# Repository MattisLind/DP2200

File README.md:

# Datapoint 2200

The restoration of this Datapoint 2200 is now finished and it is mostly working perfectly. One of the tape drives are bit finicky when it is cold though.

It was a long journey that involved creating a simulator, make extender boards and a PSU that can be used while debugging the machine to avoid getting killed (the original PSU is hazardous). In the end there were one single TTL chip that was bad.

The purpose of this repo is to describe the effort in restoring a Datapoint 2200 that I received as an IKEA-kit. This will include documenting all the parts of the machine as well as create a simulator for it.

I received this Datapoint 2200 (Version II) as a trade with a German collector for a Q1 computersystem. The 2200 was delivered as a kit, but I am pretty sure all parts are present. The goal is to revive this very interesting milestone in computer history. It can be considered as the first personal computer (depending on definition) and is also the beginning of x86 archicture whis still is omnipresent.

There are two versions of the Datapoint 2200. Version I was a serial implementation where the memory was built out of dynamic MOS shiftregisters. The reason for this was that random access memory chips wasn't available yet. The ALU was also implemented in serial fashion handling one bit at a time. This also meant that all regsisters (A,B,C,D,E,H,L) were 8-bit shiftregisters. The serial implementation of course made the CPU very slow. An instruction could take 16 microseconds to execute and this didn't include instruction fetch or memory references. Memory accesses could take up to 520 mircoseconds since the memory essentially was a long loop of bits that has to be shifted to the correct position to be accessed.

Later on Datapoint asked both Intel and Texas to design a MOS chip for the architecture of the Datapoint 2200. Both vendors came up with a chip but at that time Datapoint already decided to go for a parallell variant of the CPU using the now available RAM chips. The version II used 1k Dyanmic RAM chips (Mostek MK 4006) and a 8 bit parallell ALU using two 74181.

## Power supply

The PSU is the right half in the pricture above and sits in the back of the unit. But the CPU is not selfcontained. The 50 pin connector is connected to a backplane where the control logic for the PSU is located. Since this logic is on the hot side there a live voltages in the backplane. The transistors on the back of the big heatsink the PSU is mounted to also are a line voltage. One has to be careful when working with this PSU...

The design of the PSU is quite peculiar and is not looking like any other switch mode PSU I have seen. There is a buck-converter directly off the rectified AC input which steps down from line-voltage to around 60. The control-logic is designed to regulate to this voltage. The 60V DC levels is then converted into 5V and other outputs using a self-resonant push-pull design. There is also a crowbar protecting it so that the 60V DC may never reach above 77V.

Control-logic is on a board in the backplane.

## Simulator

I decided that a simulator would be useful to have when trying to debug and then also perhaps write small programs for this machine. I found a 8008 simulator which looked quite promising and did quite some adaptations for it to to run Datapoint 2200 code. The simulator is very much work in progress and is far from finished. I.e. non-working.

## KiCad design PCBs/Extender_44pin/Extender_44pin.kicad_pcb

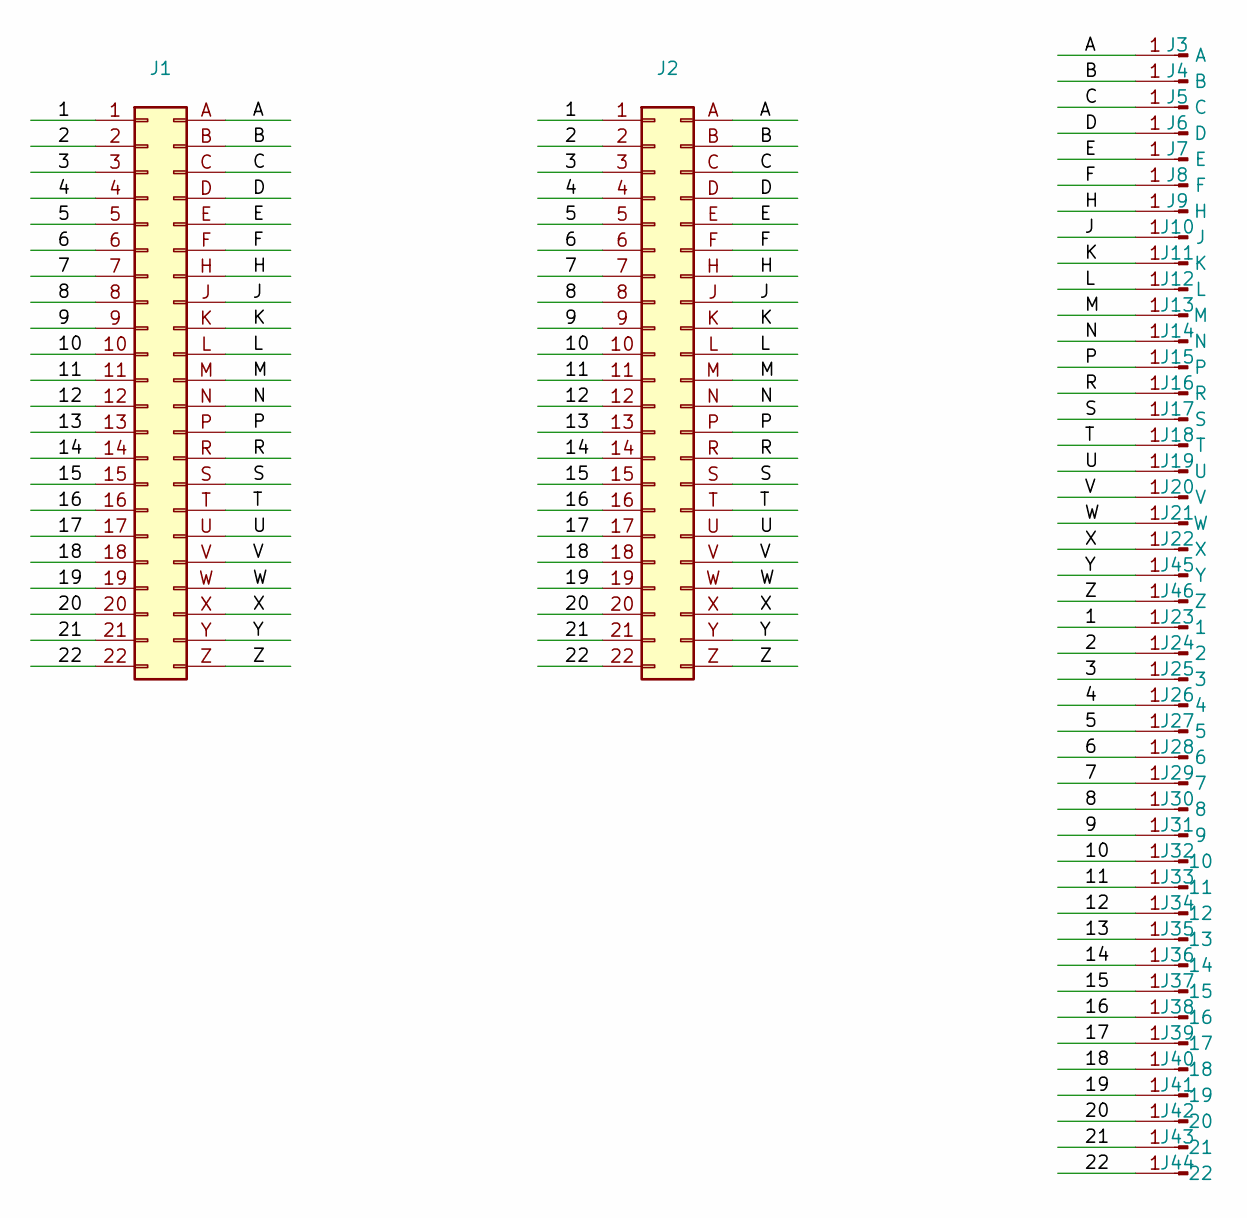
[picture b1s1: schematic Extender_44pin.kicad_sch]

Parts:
J1: Datapoint_2200_44pin_female
J2: Datapoint_2200_44pin_male
J3: A; PinHeader_1x01_P2.54mm_Vertical
J4: B; PinHeader_1x01_P2.54mm_Vertical
J5: C; PinHeader_1x01_P2.54mm_Vertical
J6: D; PinHeader_1x01_P2.54mm_Vertical
J7: E; PinHeader_1x01_P2.54mm_Vertical
J8: F; PinHeader_1x01_P2.54mm_Vertical
J9: H; PinHeader_1x01_P2.54mm_Vertical
J10: J; PinHeader_1x01_P2.54mm_Vertical
J11: K; PinHeader_1x01_P2.54mm_Vertical
J12: L; PinHeader_1x01_P2.54mm_Vertical
J13: M; PinHeader_1x01_P2.54mm_Vertical
J14: N; PinHeader_1x01_P2.54mm_Vertical
J15: P; PinHeader_1x01_P2.54mm_Vertical
J16: R; PinHeader_1x01_P2.54mm_Vertical
J17: S; PinHeader_1x01_P2.54mm_Vertical
J18: T; PinHeader_1x01_P2.54mm_Vertical
J19: U; PinHeader_1x01_P2.54mm_Vertical
J20: V; PinHeader_1x01_P2.54mm_Vertical
J21: W; PinHeader_1x01_P2.54mm_Vertical
J22: X; PinHeader_1x01_P2.54mm_Vertical
J23: 1; PinHeader_1x01_P2.54mm_Vertical
J24: 2; PinHeader_1x01_P2.54mm_Vertical
J25: 3; PinHeader_1x01_P2.54mm_Vertical
J26: 4; PinHeader_1x01_P2.54mm_Vertical
J27: 5; PinHeader_1x01_P2.54mm_Vertical
J28: 6; PinHeader_1x01_P2.54mm_Vertical
J29: 7; PinHeader_1x01_P2.54mm_Vertical
J30: 8; PinHeader_1x01_P2.54mm_Vertical
J31: 9; PinHeader_1x01_P2.54mm_Vertical
J32: 10; PinHeader_1x01_P2.54mm_Vertical
J33: 11; PinHeader_1x01_P2.54mm_Vertical
J34: 12; PinHeader_1x01_P2.54mm_Vertical
J35: 13; PinHeader_1x01_P2.54mm_Vertical
J36: 14; PinHeader_1x01_P2.54mm_Vertical
J37: 15; PinHeader_1x01_P2.54mm_Vertical
J38: 16; PinHeader_1x01_P2.54mm_Vertical
J39: 17; PinHeader_1x01_P2.54mm_Vertical
J40: 18; PinHeader_1x01_P2.54mm_Vertical
J41: 19; PinHeader_1x01_P2.54mm_Vertical
J42: 20; PinHeader_1x01_P2.54mm_Vertical
J43: 21; PinHeader_1x01_P2.54mm_Vertical
J44: 22; PinHeader_1x01_P2.54mm_Vertical
J45: Y; PinHeader_1x01_P2.54mm_Vertical
J46: Z; PinHeader_1x01_P2.54mm_Vertical

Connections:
/1: J1.1, J2.1, J23.1
/2: J1.2, J2.2, J24.1
/3: J1.3, J2.3, J25.1
/4: J1.4, J2.4, J26.1
/5: J1.5, J2.5, J27.1
/6: J1.6, J2.6, J28.1
/7: J1.7, J2.7, J29.1
/8: J1.8, J2.8, J30.1
/9: J1.9, J2.9, J31.1
/10: J1.10, J2.10, J32.1
/11: J1.11, J2.11, J33.1
/12: J1.12, J2.12, J34.1
/13: J1.13, J2.13, J35.1
/14: J1.14, J2.14, J36.1
/15: J1.15, J2.15, J37.1
/16: J1.16, J2.16, J38.1
/17: J1.17, J2.17, J39.1
/18: J1.18, J2.18, J40.1
/19: J1.19, J2.19, J41.1
/20: J1.20, J2.20, J42.1
/21: J1.21, J2.21, J43.1
/22: J1.22, J2.22, J44.1
/A: J1.A, J2.A, J3.1
/B: J1.B, J2.B, J4.1
/C: J1.C, J2.C, J5.1
/D: J1.D, J2.D, J6.1
/E: J1.E, J2.E, J7.1
/F: J1.F, J2.F, J8.1
/H: J1.H, J2.H, J9.1
/J: J1.J, J2.J, J10.1
/K: J1.K, J2.K, J11.1
/L: J1.L, J2.L, J12.1
/M: J1.M, J2.M, J13.1
/N: J1.N, J2.N, J14.1
/P: J1.P, J2.P, J15.1
/R: J1.R, J2.R, J16.1
/S: J1.S, J2.S, J17.1
/T: J1.T, J2.T, J18.1
/U: J1.U, J2.U, J19.1
/V: J1.V, J2.V, J20.1
/W: J1.W, J2.W, J21.1
/X: J1.X, J2.X, J22.1
/Y: J1.Y, J2.Y, J45.1
/Z: J1.Z, J2.Z, J46.1

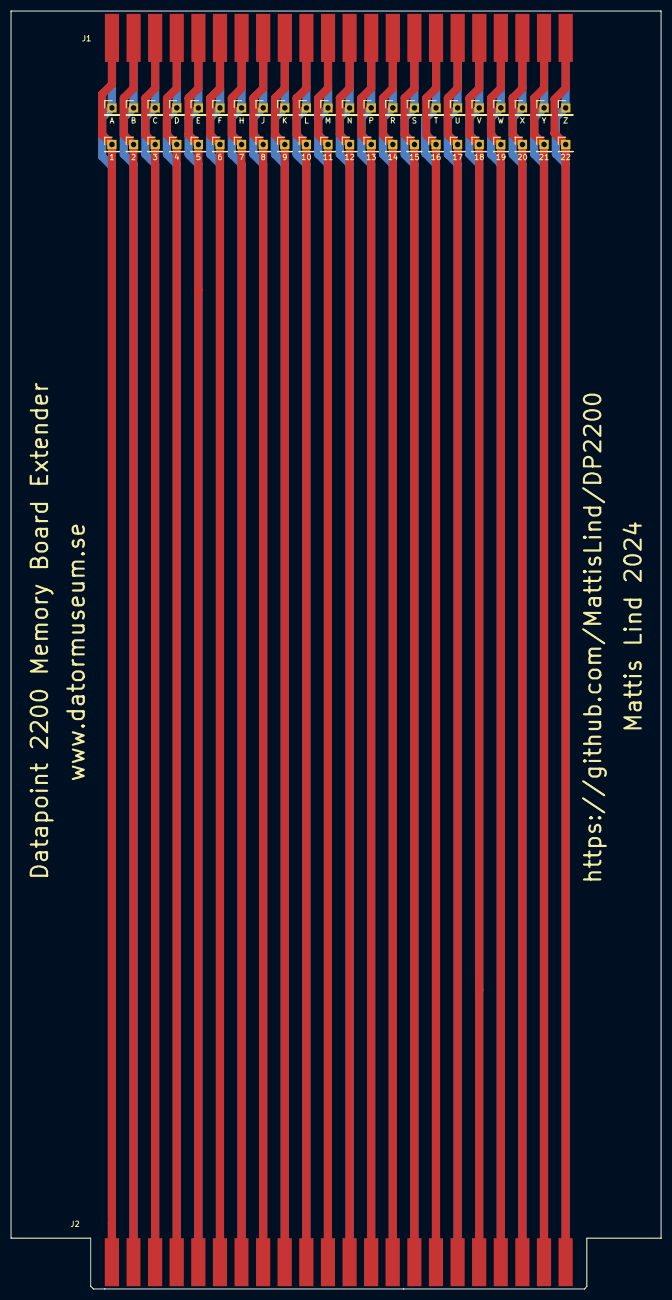
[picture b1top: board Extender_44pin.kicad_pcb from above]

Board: 2 copper layers, 119.1 x 234.2 mm, 46 parts (0 on the bottom side), 44 nets.

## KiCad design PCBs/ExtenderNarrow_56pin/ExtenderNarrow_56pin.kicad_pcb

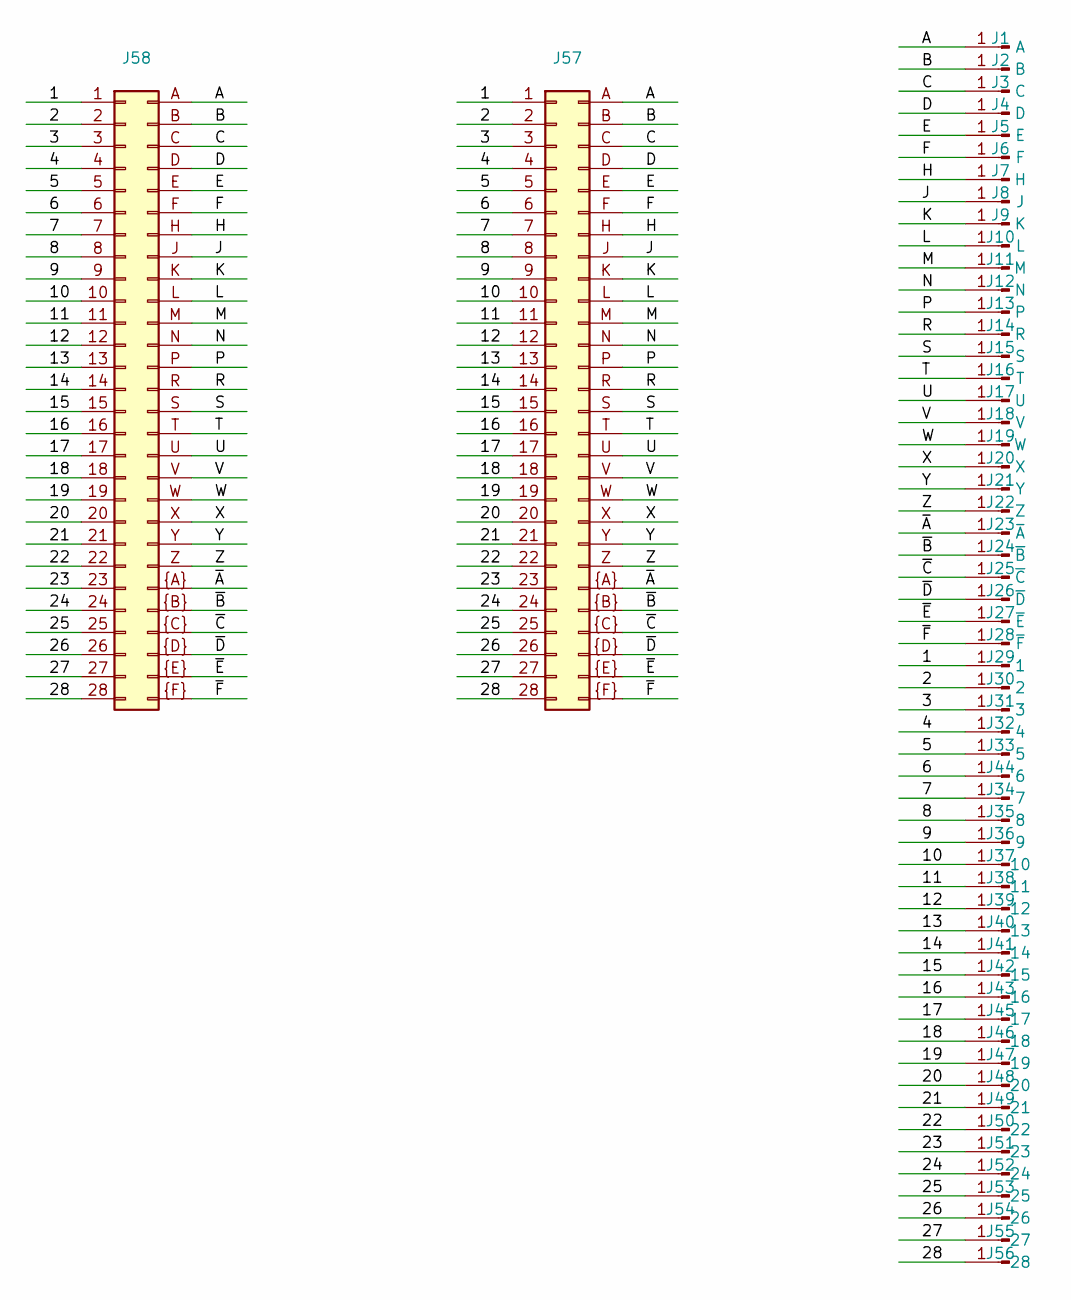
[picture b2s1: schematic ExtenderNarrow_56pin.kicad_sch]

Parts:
J1: A; PinHeader_1x01_P2.54mm_Vertical
J2: B; PinHeader_1x01_P2.54mm_Vertical
J3: C; PinHeader_1x01_P2.54mm_Vertical
J4: D; PinHeader_1x01_P2.54mm_Vertical
J5: E; PinHeader_1x01_P2.54mm_Vertical
J6: F; PinHeader_1x01_P2.54mm_Vertical
J7: H; PinHeader_1x01_P2.54mm_Vertical
J8: J; PinHeader_1x01_P2.54mm_Vertical
J9: K; PinHeader_1x01_P2.54mm_Vertical
J10: L; PinHeader_1x01_P2.54mm_Vertical
J11: M; PinHeader_1x01_P2.54mm_Vertical
J12: N; PinHeader_1x01_P2.54mm_Vertical
J13: P; PinHeader_1x01_P2.54mm_Vertical
J14: R; PinHeader_1x01_P2.54mm_Vertical
J15: S; PinHeader_1x01_P2.54mm_Vertical
J16: T; PinHeader_1x01_P2.54mm_Vertical
J17: U; PinHeader_1x01_P2.54mm_Vertical
J18: V; PinHeader_1x01_P2.54mm_Vertical
J19: W; PinHeader_1x01_P2.54mm_Vertical
J20: X; PinHeader_1x01_P2.54mm_Vertical
J21: Y; PinHeader_1x01_P2.54mm_Vertical
J22: Z; PinHeader_1x01_P2.54mm_Vertical
J23: ~{A}; PinHeader_1x01_P2.54mm_Vertical
J24: ~{B}; PinHeader_1x01_P2.54mm_Vertical
J25: ~{C}; PinHeader_1x01_P2.54mm_Vertical
J26: ~{D}; PinHeader_1x01_P2.54mm_Vertical
J27: ~{E}; PinHeader_1x01_P2.54mm_Vertical
J28: ~{F}; PinHeader_1x01_P2.54mm_Vertical
J29: 1; PinHeader_1x01_P2.54mm_Vertical
J30: 2; PinHeader_1x01_P2.54mm_Vertical
J31: 3; PinHeader_1x01_P2.54mm_Vertical
J32: 4; PinHeader_1x01_P2.54mm_Vertical
J33: 5; PinHeader_1x01_P2.54mm_Vertical
J34: 7; PinHeader_1x01_P2.54mm_Vertical
J35: 8; PinHeader_1x01_P2.54mm_Vertical
J36: 9; PinHeader_1x01_P2.54mm_Vertical
J37: 10; PinHeader_1x01_P2.54mm_Vertical
J38: 11; PinHeader_1x01_P2.54mm_Vertical
J39: 12; PinHeader_1x01_P2.54mm_Vertical
J40: 13; PinHeader_1x01_P2.54mm_Vertical
J41: 14; PinHeader_1x01_P2.54mm_Vertical
J42: 15; PinHeader_1x01_P2.54mm_Vertical
J43: 16; PinHeader_1x01_P2.54mm_Vertical
J44: 6; PinHeader_1x01_P2.54mm_Vertical
J45: 17; PinHeader_1x01_P2.54mm_Vertical
J46: 18; PinHeader_1x01_P2.54mm_Vertical
J47: 19; PinHeader_1x01_P2.54mm_Vertical
J48: 20; PinHeader_1x01_P2.54mm_Vertical
J49: 21; PinHeader_1x01_P2.54mm_Vertical
J50: 22; PinHeader_1x01_P2.54mm_Vertical
J51: 23; PinHeader_1x01_P2.54mm_Vertical
J52: 24; PinHeader_1x01_P2.54mm_Vertical
J53: 25; PinHeader_1x01_P2.54mm_Vertical
J54: 26; PinHeader_1x01_P2.54mm_Vertical
J55: 27; PinHeader_1x01_P2.54mm_Vertical
J56: 28; PinHeader_1x01_P2.54mm_Vertical
J57: Datapoint_2200_56_pin_female
J58: Datapoint_2200_56_pin_male

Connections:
/1: J29.1, J57.1, J58.1
/2: J30.1, J57.2, J58.2
/3: J31.1, J57.3, J58.3
/4: J32.1, J57.4, J58.4
/5: J33.1, J57.5, J58.5
/6: J44.1, J57.6, J58.6
/7: J34.1, J57.7, J58.7
/8: J35.1, J57.8, J58.8
/9: J36.1, J57.9, J58.9
/10: J37.1, J57.10, J58.10
/11: J38.1, J57.11, J58.11
/12: J39.1, J57.12, J58.12
/13: J40.1, J57.13, J58.13
/14: J41.1, J57.14, J58.14
/15: J42.1, J57.15, J58.15
/16: J43.1, J57.16, J58.16
/17: J45.1, J57.17, J58.17
/18: J46.1, J57.18, J58.18
/19: J47.1, J57.19, J58.19
/20: J48.1, J57.20, J58.20
/21: J49.1, J57.21, J58.21
/22: J50.1, J57.22, J58.22
/23: J51.1, J57.23, J58.23
/24: J52.1, J57.24, J58.24
/25: J53.1, J57.25, J58.25
/26: J54.1, J57.26, J58.26
/27: J55.1, J57.27, J58.27
/28: J56.1, J57.28, J58.28
/A: J1.1, J57.A, J58.A
/B: J2.1, J57.B, J58.B
/C: J3.1, J57.C, J58.C
/D: J4.1, J57.D, J58.D
/E: J5.1, J57.E, J58.E
/F: J6.1, J57.F, J58.F
/H: J7.1, J57.H, J58.H
/J: J8.1, J57.J, J58.J
/K: J9.1, J57.K, J58.K
/L: J10.1, J57.L, J58.L
/M: J11.1, J57.M, J58.M
/N: J12.1, J57.N, J58.N
/P: J13.1, J57.P, J58.P
/R: J14.1, J57.R, J58.R
/S: J15.1, J57.S, J58.S
/T: J16.1, J57.T, J58.T
/U: J17.1, J57.U, J58.U
/V: J18.1, J57.V, J58.V
/W: J19.1, J57.W, J58.W
/X: J20.1, J57.X, J58.X
/Y: J21.1, J57.Y, J58.Y
/Z: J22.1, J57.Z, J58.Z
/~A: J23.1, J57.~{A}, J58.~{A}
/~B: J24.1, J57.~{B}, J58.~{B}
/~C: J25.1, J57.~{C}, J58.~{C}
/~D: J26.1, J57.~{D}, J58.~{D}
/~E: J27.1, J57.~{E}, J58.~{E}
/~F: J28.1, J57.~{F}, J58.~{F}

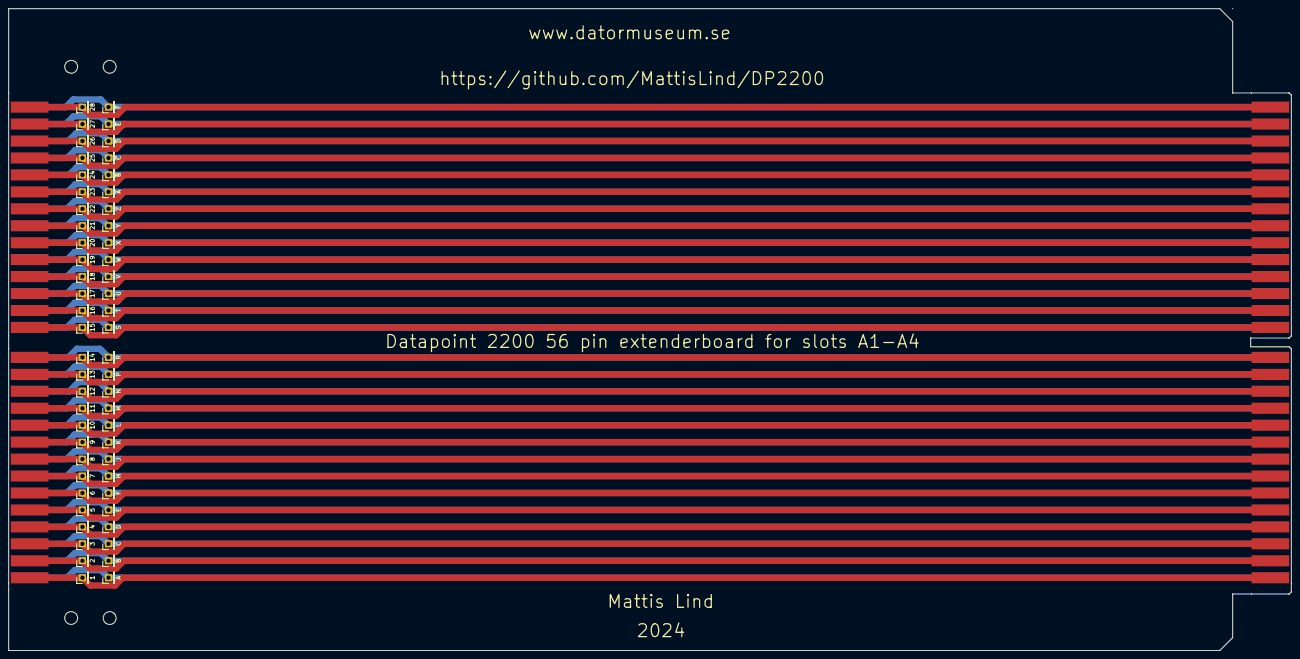
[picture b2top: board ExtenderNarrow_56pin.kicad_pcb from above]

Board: 2 copper layers, 299.7 x 150.0 mm, 58 parts (0 on the bottom side), 56 nets.

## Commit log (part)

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2023-10-23 Adding a very preliminary simulator. It even doesn't simulate yet...
2023-10-24 Fixed up errors in the simulator to make it compile.
2023-10-24 Added a note on MACOS only.
2023-10-24 Added EXIT command...
2023-10-24 Cleanup.
2023-10-24 Handling upper / lowervase better.
2023-10-24 Wrapping the simulator in a class to be able to instantiate it and give a ref to it to use from the command handler.
2023-10-24 Yet more C++ restructuring.
2023-10-24 Referencing the cpu instance from all the window instances.
2023-10-25 Adding more commands.
2023-10-25 Refactoring casette tape into own class.
2023-10-26 Work in progress - use ncurses forms instead
2023-10-28 Temporarily add experimental code that need to be refactored later on just to save it.
2023-10-28 Merged in code from forms.cpp
2023-10-28 Fixed a pointer that wasn't initialized properly.
2023-10-28 Added the tap-file reader - to be refactored into the simulator.
2023-10-28 Added function to read in the boot code to memory.
2023-10-29 Added tapes and tape analyzer.
2023-10-29 Added CPU registers to the register display.
2023-10-29 Refactor of how to update the data from form.
2023-10-29 Fixed some warnings.
2023-10-29 Now it is possible to load the boot code and step through instruction.
2023-10-29 Added a screen dump.
2023-10-29 Adding screen dump to README.md
2023-10-29 Yet more changes to README.md.
2023-10-29 Added a underline for the location in memory pointed to be P. Added QUIT command to do the same as EXIT.
2023-10-29 Added stack view.
2023-10-30 Removed some unused vars.
2023-10-30 Refactoring and fix for not updating ascii printout when changing memory content.
2023-10-30 Yet more refactoring.
2023-10-30 Forgot to add dp2200_cpu_sim.h.
2023-10-30 Fixed bug when pressing backspace when empty command. Added new screen capture.
2023-10-31 Now it can run instruction. Added an instruction trace as well. Halts on unimplemented instructions
2023-10-31 Updated screen shot.
2023-10-31 Added breakpoints.
2023-11-01 DEV-0: Adding more logs to understan why the Avassa API times out and if this can be handled somehow.
2023-11-01 Added a skeleton for a IO handling framework.
2023-11-01 Refactor. cassetteTape instances are now a part of the cassetteDevice.
2023-11-01 Found a bug with RETURN.
2023-11-02 More updates and refactor.
2023-11-02 Added a Makefile.
2023-11-02 Updated readme.
2023-11-03 Added some tape handling. Still a lot of work needed.
2023-11-03 Seems to be loading correctly.
2023-11-04 Refactor to use pointers to callbackrecord objects.
2023-11-04 Using functor syntax for callbacks.
2023-11-04 Passing pointer to callback record back in the callback so that it can be used as an unique ID for the record.
2023-11-04 Adding all outstanding timers in cassette io device to a vector so that we can cancel all of them when we get a TSTOP.
2023-11-05 Fixes in makefile and other to make it compile in Linux.
2023-11-07 Save work so that I can work on some other idea.
2023-11-07 Substantial rewrite of how the cpu handles time. No manage to get to where it accesses screen.
2023-11-08 Major refactor. Ripping out window classes from main.cpp.
2023-11-08 Added Dockerfile to make it easier to verify build on Linux.
2023-11-09 Adding display handler.
2023-11-09 Now we get some output on the screen and it waits for input from the keyboard
2023-11-09 Forgot to add files again...
2023-11-09 More files to add..
2023-11-10 Now actually is able to start the CTIS opeating system.
2023-11-10 Added keyboard handling.
2023-11-10 Fixed a bit of keyboard translation.
2023-11-11 Rewrote the cassette tape system to make it less complex.
2023-11-11 Added yield command.
2023-11-12 Better error handling.
2023-11-12 Handling too small window better.
2023-11-12 Added better help.
2023-11-12 Better formatting of help text.
2023-11-12 Start refactoring register-view to have several forms.
2023-11-12 Stupid bug sneaked in.
2023-11-12 Cleaning.
2023-11-12 Moved files around a bit.
2023-11-12 Moving around code a bit.
2023-11-12 Removed a bit too much.
2023-11-12 Refactor.
2023-11-12 Fix for updating field bug.
2023-11-12 Refactor in progress.
2023-11-16 Work on octal display.
2023-11-26 Work in progress - refactoring forms handling.
2023-11-26 Fixed update bug. Seems to be working fine.
2023-11-26 Fixed build in Linnux.
2023-11-26 Added an octal mode.
2023-11-26 Fixed some bugs.
2023-11-26 Som more fixes.
2023-11-26 Fixed some more things.
2023-11-27 Upodated text and movie clip.
2023-11-28 Now the keyboard test is able to start since we added a dummy parallell adapter.
2023-11-30 Trying to handle window resize - not working that good unfortunately.
2023-11-30 Added a Games.tap file.
2023-12-09 Added support for 9380 floppy but it cannot boot. Not sure why? Bad disks? Problem with implementation?
2023-12-09 Fixed build on Linux.
2023-12-09 Now it at least boots from disk 011.IMD correctly, but it want to so a EX_WRITE towards the disk which is not implemented currently.
2023-12-09 Setting the disk read-only solves the problem for now...
2023-12-09 Fixes to detach command.
2023-12-09 Added files for DOS. Updated README.
2023-12-17 Added support for local printer and dummy support for servo printer.
2023-12-17 Changed so that the IMD file is read into memory.
2023-12-17 Added support for raw disk images that are 256256 bytes exactly.
2023-12-17 Fixed bug in detach which unfortunately revealed a problem with IMD write back. Fix is coming...
2023-12-18 Found some interesting problems by compiling under Linux.
2023-12-19 Added write protect and writeback switches. rewrite seems to work.
2023-12-20 Added support autoincrement of cursor position and scroll down.
2023-12-24 Added support for LEFT and RIGHT arrow keys and deleting characters in string.
2023-12-24 Fixed so that it is possible to insert characters as well.
2023-12-24 Handle correctly when pressing CR.
2023-12-25 Added command history.
2023-12-25 Fixed so that empty commands is not stored in history.
2023-12-25 Added a warning message when mounting an IMD with bad blocks.
2023-12-25 Fixes so it compiles on Linux.
2023-12-25 Added wav processing code.
2023-12-26 Revert "Fixes so it compiles on Linux."
    This reverts commit f994382cd121765a71f70c1bbd33611eb1de455c.
2023-12-26 Fixes for linux.
2023-12-26 More fixes to have Wall and Werror back.
2023-12-26 Introduced problem in the makefile that caused problems in macos.
2023-12-26 Now works in linux with Wall and Werror.
2023-12-26 Regression due to adding code that reports warning for corrupted disks.
2023-12-26 Spelling..
2023-12-30 New algorithm.
2024-01-02 Trimmed weights for score.
2024-01-02 Added DOS.D tapes.
2024-01-03 Added preliminary 9350 support. Need more to get it to work.
2024-01-07 More work on getting 9350 and 9370 support. Not tested yet.
2024-01-09 Using 8 bit ioaddresses rather than four bit to be compatible with newer devices.
2024-01-09 9370 support seems to be at least somewhat working. Formatting has some work remaining.
2024-01-10 Better logging.
2024-01-10 Now 9350 is working as well.
2024-01-18 Added yet more 5500 support and fixed a new command SET CPU=5500 or SET CPU=2200 to show / not show the X register.
2024-01-21 Removed uncessesary logging.
2024-01-23 Added missing 5500 instruction.
2024-01-24 Adding more 5500 instructions and getting futher in DOS.D generation process.
2024-01-27 Fixing more 5500 instructions.
2024-02-03 Reworking cassette tape and fixing problem with gaps. Interrupts are now using CPU time instead of real time.
2024-02-04 Yet more fixes for 5500 and adding a memory watcher.
2024-02-05 Refactoring memory handling to use read and write ops.
2024-02-05 Fixing disk drive disk address calculation which was totally wrong.
2024-02-06 Found a bug / lack of implementatiomn of 9370 disk read..
2024-02-06 Just not halting when a cassette write is issued.
2024-02-07 Added just the casette stuff.
2024-02-08 Refactord memory handling to be able to add 5500 memory management.
2024-02-16 Adding new style of disassembler. First step. Reworked memory handling and added 5500 memory management.
2024-02-17 Refactored disassembly. Now 5500 instruction should be handled better.
2024-02-17 Added debug display of base register and sector table.
2024-02-17 Added 5500 interrupt handling. Added STL instruction.
2024-02-18 Fixed INCP bug. Fixed trace disassmbler.
2024-02-18 Fixed missing instruction and added octal trace.
2024-02-19 Added missing instructions. Fixed problem with PROM write-only.
2024-02-19 Bugfixes...
2024-02-19 Fixed DPL and DPS instruction in disassembler.
2024-02-19 Fixed crash if accessing unsupported device when single stepping
2024-02-21 Added better tracing capabilities to easier disassemble code using the simulator.
2024-02-22 Adding a 5500 disassembly.
2024-02-23 Updated 5500 disassembly.
2024-02-23 More cleanup of the disassembly.
2024-02-23 Added a bunch of more comments. analysed keypresses.
2024-02-23 Added a bunch of more comments. analysed more keypresses. Until R
2024-02-24 Yet more fixes of the disassembly.
2024-02-24 More updates.
2024-02-24 Found the RESTART entrypoint. Fixed Delayed DEC READY for 1 ms to make the 5500 boot code to work.
2024-02-25 Fixed an issue with enable interrupt.
2024-03-02 Fixed cassette handling a bit.
2024-03-02 Fixing so that restart do a restart on the 5500.
2024-03-02 Fixed command history bug. Fixed crash if accessing tape when no tape installed. Floppy drive has auto-increment buffers as it seems.
2024-03-03 Fixed a bug in floppy handling.
2024-03-04 Added missing instruction to get chess program running and fixed a bug.
2024-03-05 Improved cassette handling. Shift instruction lacked implicit handling.
2024-03-05 Added MIN instruction .
2024-03-09 Trying to handle removal of cassette better.
2024-03-11 Make it read diskettes with missing sector.
2024-05-20 Added narrow 56 pin narrow extender.
2024-05-20 Added breadboard.
2024-05-21 Added wide 56 pin extender board.
2024-05-24 Added 72 pin extender
2024-05-25 Adding 44 pin extender.
2024-05-25 Added 36 pin extender
2024-05-25 Updates of extender boards.
2024-05-26 Yet more updates to the boards.
2024-07-16 Added BASIC, Assembler and GEDIT.
2024-07-17 Fixed a bug dealing with parity. The 2200 is opposite of the 8008 in regards to parity.
2024-10-02 Adding DatapointCassetteTool.
2024-11-01 Made some testing. Seems to work. Need real world testing.
2024-11-03 Update DatapointCassetteTool.ino
    Now running on STM32 board!
2024-11-03 Update DatapointCassetteTool.ino
    Added tstpro processor test as a hard coded buffer
2025-05-27 Added fixes to dpwav2tap.
2025-05-27 Fixed the Paged Load PL A instruction
2025-07-01 Fixed a lot of issues in DP5500 mode since we now have proper diagnostics to use.
2025-07-01 Yet more 5500 fixes.
2025-08-15 5500 fixes.
2025-08-18 Latest fixes.
2025-08-18 More fixes..
2025-10-19 Fixing so that a trailing sync pattern is sent and use LSB first data.
2025-11-15 Created a tool to write tap-formatted files to a cassette.
2025-11-16 Added refactord variants that has less work done in the ISR.
2025-11-16 Adding test tap-files.
2025-11-17 New decoder that outputs a tap file.
2025-11-17 Fixing shim and linux wrapper.
2025-11-17 Fixing things.
2025-11-17 Update tap_fm_tx_sketch.hpp
    Compiles in Arduino
2025-11-17 64 bit acc variant
    64 bit acc variant
2025-11-18 Slave mode and use of timer to produce the clock.
2025-11-18 The short test was wrong.
2025-11-20 Update tap_fm_sketch_64bitacc_critsections.hpp
    Debugging
2025-11-21 Fixing interrupts and making it compile again in Linux.
2025-11-22 More cleaning up and testing.
2025-11-22 Update tap_fm_sketch_64bitacc_critsections.hpp
    Fixes!
2026-04-20 Fix uninitialized logicalAddress and sector clear in track validation
    - dp2200_cpu_sim.cpp: set logicalAddress when bypassing MMU translation
    - FloppyDrive.cpp: clear sectorType sequentially (sectorMap was uninitialized at that point)
